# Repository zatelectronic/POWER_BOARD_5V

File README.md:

<div align="center">

# POWER BOARD +5V

**Placa de alimentação DC-DC step-down (buck converter) com entrada de 24V e saída regulada de 5V, baseada em regulador chaveado SMD de alta eficiência**

</div>

---

## 📋 Índice

- [POWER BOARD +5V](#power-board-5v)
  - [📋 Índice](#-índice)
  - [Visão Geral](#visão-geral)
  - [Renders 3D](#renders-3d)
  - [Funcionalidades](#funcionalidades)
  - [Diagrama de Funcionamento](#diagrama-de-funcionamento)
  - [Especificações Técnicas](#especificações-técnicas)
  - [Lista de Materiais](#lista-de-materiais)
  - [Pinagem dos Conectores](#pinagem-dos-conectores)
    - [DC IN — Entrada (lado esquerdo)](#dc-in--entrada-lado-esquerdo)
    - [DC OUT — Saída (lado direito)](#dc-out--saída-lado-direito)
    - [Pontos de Teste](#pontos-de-teste)
  - [Aplicações](#aplicações)
  - [Estrutura do Repositório](#estrutura-do-repositório)
  - [Como Usar](#como-usar)
    - [Instalação básica](#instalação-básica)
    - [Dica de Integração](#dica-de-integração)
  - [⚠️ Avisos de Segurança](#️-avisos-de-segurança)
  - [Sobre](#sobre)

---

## Visão Geral

**POWER BOARD +5V** é uma placa de alimentação DC-DC do tipo **buck converter (step-down)**, projetada pela **ZAT ELECTRONIC** utilizando **KiCad 10**. A placa converte uma tensão de entrada de **+24VDC** em uma saída regulada e estável de **+5VDC / 3A**, utilizando o regulador chaveado **LM2596S-5** no encapsulamento TO-263-5 (SMD).

O design é compacto e totalmente SMD, com conexões de entrada e saída por **pads de solda** expostos diretamente na PCB. A placa inclui **fusível de proteção SMD 3A**, **diodo Schottky** de roda livre, **indutor de 33µH** e capacitores eletrolíticos de alta capacidade para filtragem e estabilidade da saída.

> ⚡ Topologia **buck converter** de alta eficiência — ideal para sistemas embarcados, painéis de controle industrial e projetos que alimentam microcontroladores e periféricos a partir de fontes de 24VDC.

---

## Renders 3D

<div align="center">

*Vista superior — regulador LM2596S-5, indutor, capacitores eletrolíticos e fusível SMD*

<br/>

*Vista isométrica — layout compacto com pads DC IN e DC OUT nas extremidades*

</div>

---

## Funcionalidades

- ✅ **Regulador chaveado LM2596S-5** (TO-263-5 SMD) — saída fixa de 5V, até 3A
- ✅ **Topologia buck converter** — alta eficiência em comparação com reguladores lineares
- ✅ **Entrada 24VDC** — compatível com fontes industriais e painéis de automação
- ✅ **Saída 5VDC / 3A** — alimentação estável para microcontroladores e periféricos
- ✅ **Fusível SMD 3A** (encapsulamento 1808/2410) — proteção contra sobrecorrente na entrada
- ✅ **Diodo Schottky SS54** (SMA SMD) — diodo de roda livre de alta velocidade
- ✅ **Indutor 33µH** (12×12mm) — núcleo de potência para o estágio de conversão
- ✅ **Capacitor de entrada 100µF/35V** (SMD eletrolítico) — filtragem da tensão de entrada
- ✅ **Capacitor de saída 680µF/16V** (SMD eletrolítico) — filtragem e estabilidade da saída
- ✅ **4 pontos de teste (TP1–TP4)** — facilidade de medição e diagnóstico em bancada
- ✅ **Pads de conexão expostos** — DC IN (+24V / GND) e DC OUT (+5V / GND)
- ✅ **Layout totalmente SMD** — compacto e adequado para integração em painéis

---

## Diagrama de Funcionamento

```
DC IN (+24V) ──[F1 3A]──[D1 SS54]──┬──────────► VIN  [U1 LM2596S-5]  OUT ──┬──[L1 33µH]──┬──► DC OUT (+5V)
                                   │                       │                  │             │
                         [C1 100µF/35V]              GND / ~ON/OFF      [D2 SS54]     [C2 680µF/16V]
                                   │                       │            (roda livre)        │
                                  GND                     GND                 │            GND
                                                                             GND
                                    FB do U1 ◄──────────────────────────────────────── +5V

DC IN (GND) ──────────────────────────────────────────► DC OUT (GND)

TP1, TP2 → pontos de teste na entrada
TP3, TP4 → pontos de teste na saída
```

---

## Especificações Técnicas

| Parâmetro | Valor |
|-----------|-------|
| **Topologia** | Buck Converter (Step-Down) |
| **Regulador** | LM2596S-5 (TO-263-5 SMD) |
| **Tensão de Entrada** | 24VDC |
| **Tensão de Saída** | 5VDC (fixa) |
| **Corrente de Saída máx.** | 3A |
| **Potência máxima de saída** | 15W |
| **Diodo de roda livre** | SS54 — Schottky 5A / 40V (SMA SMD) |
| **Indutor** | 33µH — 12×12×8mm |
| **Capacitor de entrada** | 100µF / 35V (eletrolítico SMD) |
| **Capacitor de saída** | 680µF / 16V (eletrolítico SMD) |
| **Fusível** | 3A (SMD 1808/2410) |
| **Pontos de teste** | 4x (TP1, TP2, TP3, TP4) |
| **Conexões** | Pads de solda expostos (DC IN / DC OUT) |
| **Ferramenta de Projeto** | KiCad 10 |
| **Tipo de montagem** | SMD |

---

## Lista de Materiais

| Ref | Componente | Valor / Parte | Encapsulamento |
|-----|-----------|--------------|----------------|
| U1 | Regulador Chaveado | LM2596S-5 | TO-263-5 SMD |
| L1 | Indutor de Potência | 33µH | 12×12×8mm |
| D2 | Diodo Schottky (roda livre) | SS54 — 5A / 40V | SMA SMD |
| D1 | Diodo Schottky (proteção contra inversão) | SS54 — 5A / 40V | SMA SMD |
| C1 | Capacitor Eletrolítico (entrada) | 100µF / 35V | SMD Eletrolítico 10×10mm |
| C2 | Capacitor Eletrolítico (saída) | 680µF / 16V | SMD Eletrolítico 10×12,5mm |
| F1 | Fusível de Proteção | 3A | SMD 1808/2410 |
| TP1–TP4 | Pads de solda / teste | 10 × 4 mm | SMD |

---

## Pinagem dos Conectores

A placa utiliza **pads de solda expostos** nas extremidades para conexão da entrada e saída. Não há conectores PTH — a ligação é feita diretamente por fios soldados ou trilhas de PCB mãe.

### DC IN — Entrada (lado esquerdo)

| Pad | Sinal | Descrição |
|-----|-------|-----------|
| + | +24V | Tensão de entrada positiva |
| − | GND | Terra / Negativo |

### DC OUT — Saída (lado direito)

| Pad | Sinal | Descrição |
|-----|-------|-----------|
| + | +5V | Tensão de saída regulada |
| − | GND | Terra / Negativo |

### Pontos de Teste

| Ref | Localização | Função |
|-----|-------------|--------|
| TP1 | Entrada | Medição +24V |
| TP2 | Entrada | Medição GND entrada |
| TP3 | Saída | Medição +5V |
| TP4 | Saída | Medição GND saída |

---

## Aplicações

- 🏭 **Automação industrial** — alimentação de CLPs, sensores e módulos a partir de barramentos 24V
- 🤖 **Projetos com Arduino e ESP32** — conversão de 24V industrial para 5V de lógica
- 💡 **Painéis de iluminação LED** — alimentação de controladoras a partir de fonte 24V
- 🔌 **Sistemas embarcados** — fonte embarcada compacta em projetos de hardware customizado
- 📡 **IoT industrial** — alimentação de gateways e módulos de comunicação
- 🖥️ **Painéis de controle** — fonte auxiliar de 5V integrada ao painel principal 24V

---

## Estrutura do Repositório

```
POWER_BOARD_5V/
├── POWER_BOARD_5V.kicad_pro      # Arquivo de projeto KiCad 10
├── POWER_BOARD_5V.kicad_sch      # Esquemático: capa A2 (índice das folhas)
├── BUCK.kicad_sch                # Folha 02: buck LM2596S-5
├── CONN.kicad_sch                # Folha 03: pads DC IN / DC OUT + PWR_FLAG
├── POWER_BOARD_5V.kicad_pcb      # Layout da PCB (KiCad 10)
├── POWER_BOARD_5V.kicad_prl      # Configurações locais
├── POWER_BOARD_5V.kicad_dru      # Regras customizadas (vazio: version 1)
├── Zat_TitleBlock.kicad_wks      # Title block ZAT ELECTRONIC
├── packages3D/                   # Modelos 3D arquivados (referência)
├── imagem_1.png                  # Render 3D superior
├── imagem_2.png                  # Render 3D isométrico
├── LEIA-ME_REVISAO_R01.md        # O que mudou na revisão R01
└── README.md
```

---

## Como Usar

### Instalação básica

```
Fonte 24VDC (+) ────► Pad DC IN (+24V)
Fonte 24VDC (-) ────► Pad DC IN (GND)

Carga 5VDC      ────► Pad DC OUT (+5V)
Carga GND       ────► Pad DC OUT (GND)
```

### Dica de Integração

> 🔧 Para integração em PCB mãe, solde fios diretamente nos pads DC IN e DC OUT, ou projete a placa mãe com pads compatíveis para encaixe direto. Respeite a polaridade indicada na serigrafia (+24V / GND / +5V).

---

## ⚠️ Avisos de Segurança

> 🔴 **ATENÇÃO**

- **Não inverta a polaridade** na entrada — o fusível protege contra sobrecorrente, mas a inversão pode danificar o regulador.
- Respeite a **corrente máxima de 3A** na saída para não danificar o LM2596S-5.
- O regulador e o indutor podem **aquecer durante operação** em cargas próximas ao limite — garanta ventilação adequada.
- **Verifique a tensão de entrada** antes de conectar — tensões acima de 40V danificam o regulador.
- Utilize o **fusível SMD 3A** correto — nunca o substitua por um de valor superior sem analisar o circuito.

---

## Sobre

<div align="center">

Projetado por **ZAT ELECTRONIC**

*POWER BOARD +5V — Made in Brazil 🇧🇷*

</div>

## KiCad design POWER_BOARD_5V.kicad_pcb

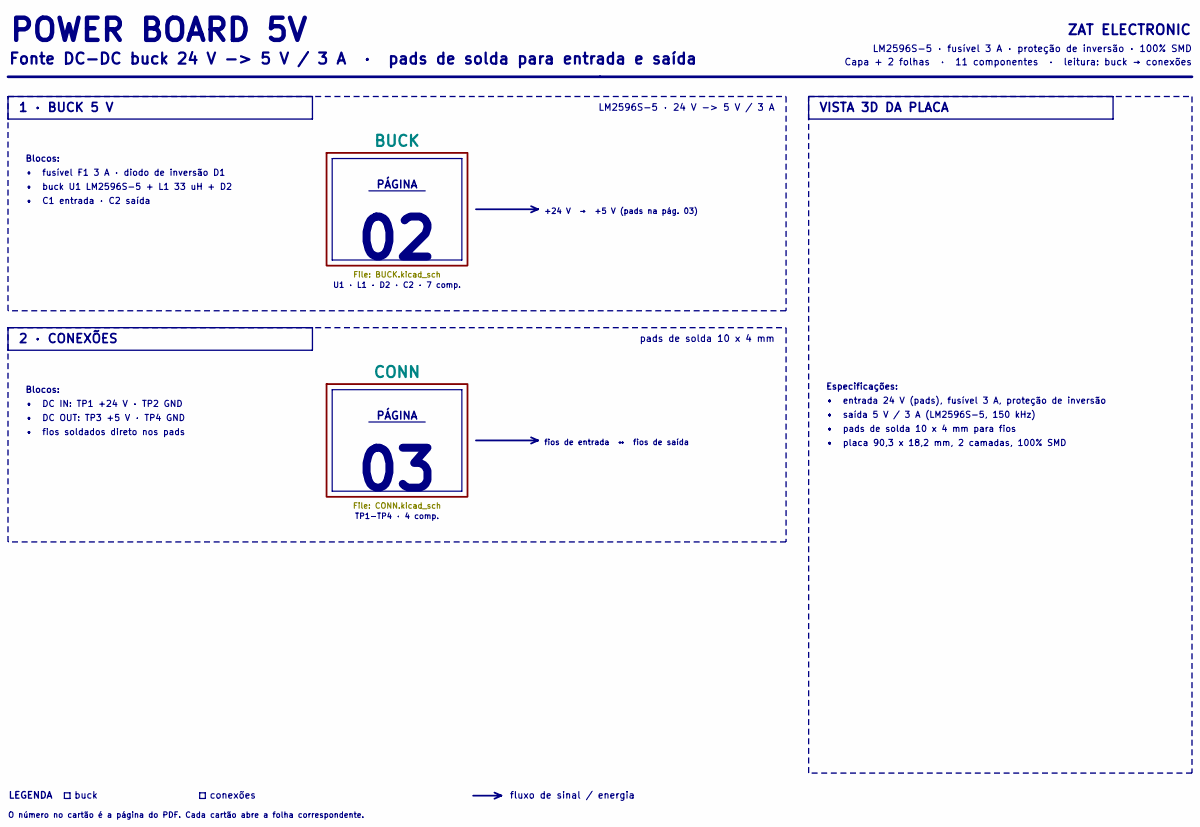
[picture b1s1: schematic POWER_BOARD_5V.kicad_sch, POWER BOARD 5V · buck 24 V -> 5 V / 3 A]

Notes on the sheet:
Capa + 2 folhas · 11 componentes · leitura: buck → conexões
Fonte DC-DC buck 24 V -> 5 V / 3 A · pads de solda para entrada e saída
buck
PÁGINA
• pads de solda 10 x 4 mm para fios
• DC OUT: TP3 +5 V · TP4 GND
• DC IN: TP1 +24 V · TP2 GND
conexões
• buck U1 LM2596S-5 + L1 33 uH + D2
VISTA 3D DA PLACA
• fios soldados direto nos pads
ZAT ELECTRONIC
1 · BUCK 5 V
Blocos:
• entrada 24 V (pads), fusível 3 A, proteção de inversão
LM2596S-5 · fusível 3 A · proteção de inversão · 100% SMD
fluxo de sinal / energia
LM2596S-5 · 24 V -> 5 V / 3 A
LEGENDA
pads de solda 10 x 4 mm
• C1 entrada · C2 saída
2 · CONEXÕES
+24 V → +5 V (pads na pág. 03)
Especificações:
• saída 5 V / 3 A (LM2596S-5, 150 kHz)
fios de entrada ↔ fios de saída
• placa 90,3 x 18,2 mm, 2 camadas, 100% SMD
• fusível F1 3 A · diodo de inversão D1
U1 · L1 · D2 · C2 · 7 comp.
POWER BOARD 5V
TP1-TP4 · 4 comp.
O número no cartão é a página do PDF. Cada cartão abre a folha correspondente.

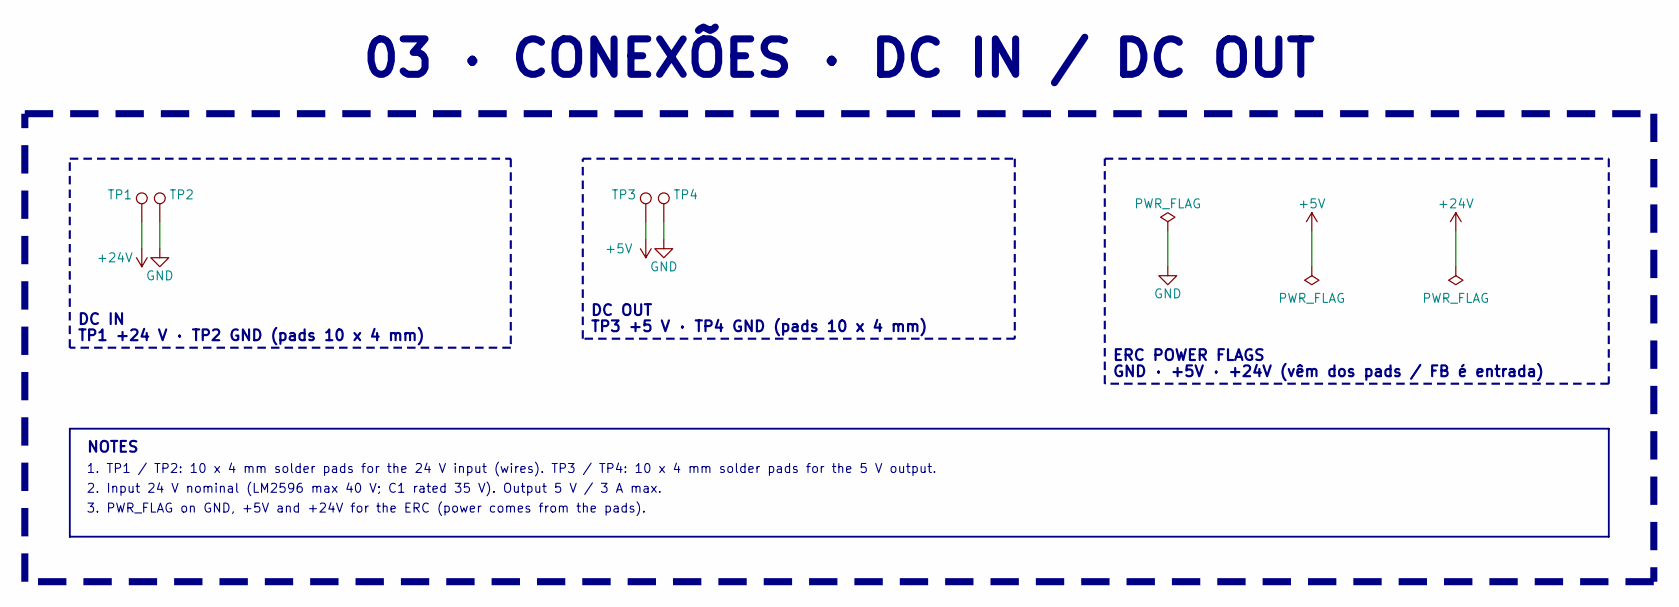
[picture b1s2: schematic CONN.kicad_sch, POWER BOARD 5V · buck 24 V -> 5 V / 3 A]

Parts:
TP1, TP2, TP3, TP4: PAD_10x4mm; TestPoint_Pad_10.0x4.0mm; MPN S1751-46R; Digi-Key_PN 952-1478-1-ND

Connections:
+5V: TP3.1 (1_1); also elsewhere on the board
+24V: TP1.1 (1_1); also elsewhere on the board
GND: TP2.1 (1_1), TP4.1 (1_1); also elsewhere on the board

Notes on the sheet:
ERC POWER FLAGS
2. Input 24 V nominal (LM2596 max 40 V; C1 rated 35 V). Output 5 V / 3 A max.
GND · +5V · +24V (vêm dos pads / FB é entrada)
NOTES
03 · CONEXÕES · DC IN / DC OUT
DC IN
DC OUT
TP3 +5 V · TP4 GND (pads 10 x 4 mm)
TP1 +24 V · TP2 GND (pads 10 x 4 mm)
1. TP1 / TP2: 10 x 4 mm solder pads for the 24 V input (wires). TP3 / TP4: 10 x 4 mm solder pads for the 5 V output.
3. PWR_FLAG on GND, +5V and +24V for the ERC (power comes from the pads).

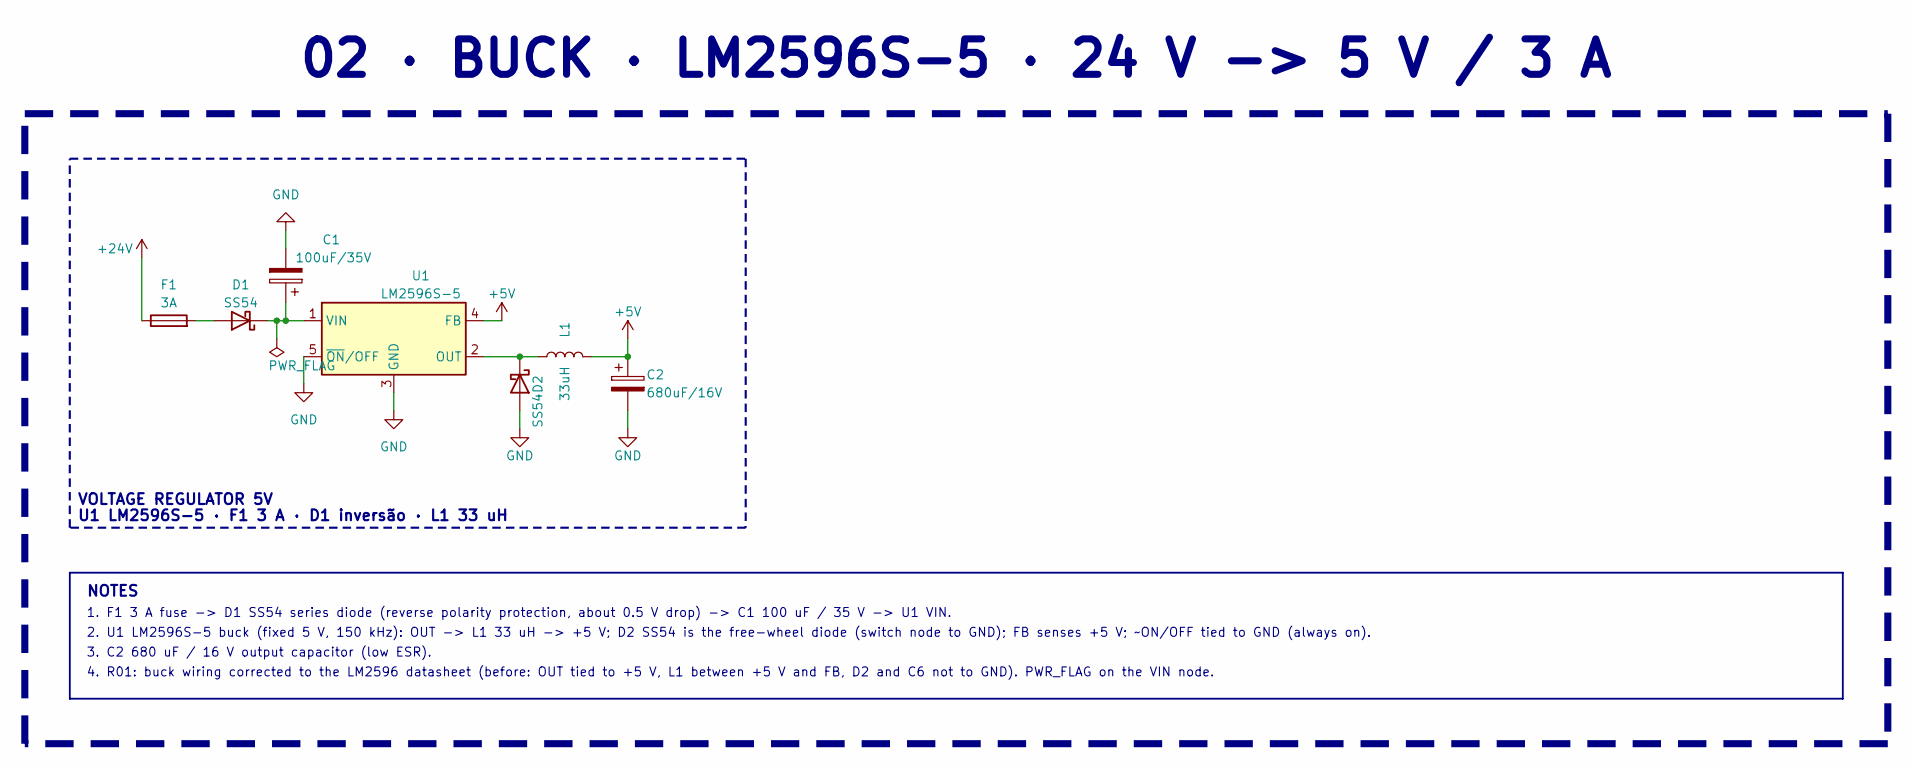
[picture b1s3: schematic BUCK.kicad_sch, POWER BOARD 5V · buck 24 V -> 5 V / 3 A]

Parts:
C1: 100uF/35V; CP_Elec_10x10
C2: 680uF/16V; CP_Elec_10x12.5
D1, D2: SS54; D_SMA
F1: 3A; Fuse_2010_5025Metric_Pad1.52x2.65mm_HandSolder_1808-2410
L1: 33uH; L_12x12mm_H8mm_33uH
U1: LM2596S-5; TO-263-5_TabPin3

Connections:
+5V: C2.1, L1.1, U1.4 (FB); also elsewhere on the board
+24V: F1.1; also elsewhere on the board
GND: C1.2, C2.2, D2.2 (A), U1.3 (GND), U1.5 (~ON/OFF); also elsewhere on the board
unnamed: D1.2 (A), F1.2
unnamed: C1.1, D1.1 (K), U1.1 (VIN)
unnamed: D2.1 (K), L1.2, U1.2 (OUT)

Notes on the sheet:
U1 LM2596S-5 · F1 3 A · D1 inversão · L1 33 uH
2. U1 LM2596S-5 buck (fixed 5 V, 150 kHz): OUT -> L1 33 uH -> +5 V; D2 SS54 is the free-wheel diode (switch node to GND); FB senses +5 V; ~ON/OFF tied to GND (always on).
02 · BUCK · LM2596S-5 · 24 V -> 5 V / 3 A
NOTES
VOLTAGE REGULATOR 5V
4. R01: buck wiring corrected to the LM2596 datasheet (before: OUT tied to +5 V, L1 between +5 V and FB, D2 and C6 not to GND). PWR_FLAG on the VIN node.
3. C2 680 uF / 16 V output capacitor (low ESR).
1. F1 3 A fuse -> D1 SS54 series diode (reverse polarity protection, about 0.5 V drop) -> C1 100 uF / 35 V -> U1 VIN.

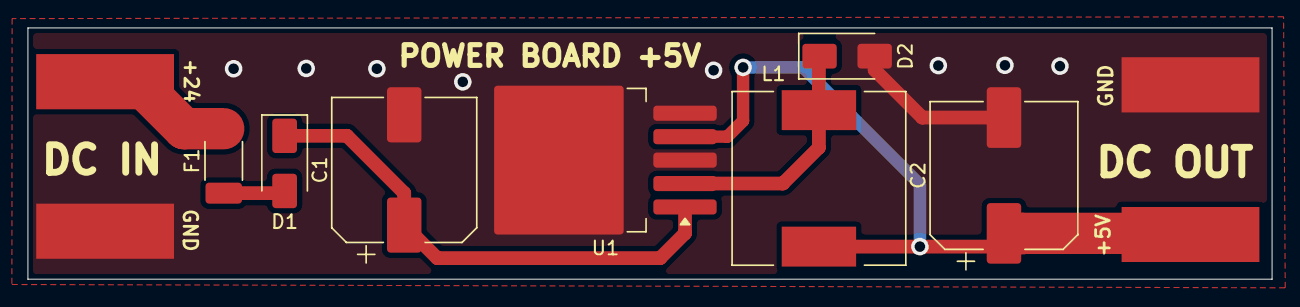
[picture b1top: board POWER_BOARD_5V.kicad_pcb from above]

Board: 2 copper layers, 90.3 x 18.2 mm, 11 parts (0 on the bottom side), 6 nets.

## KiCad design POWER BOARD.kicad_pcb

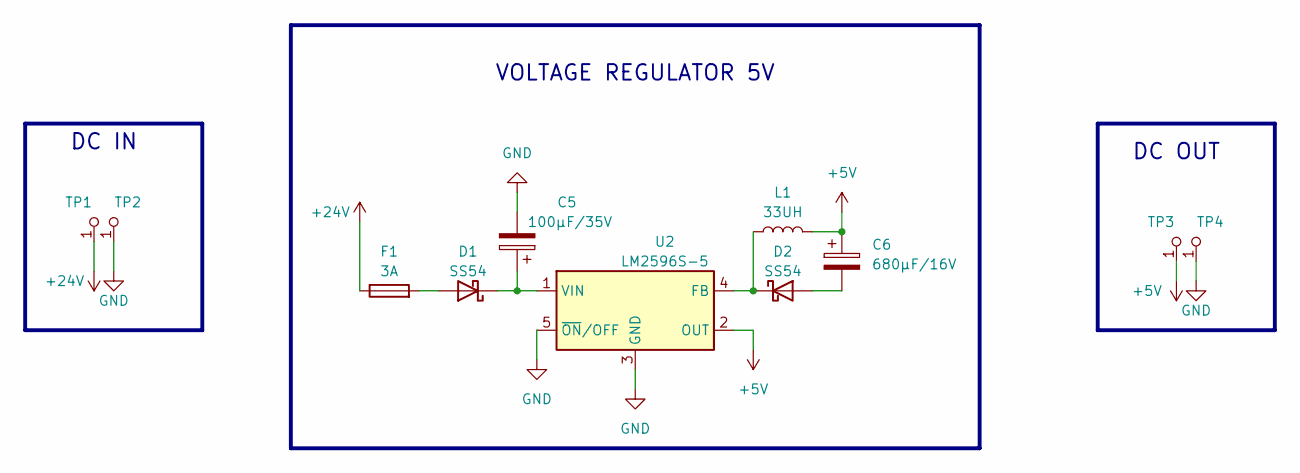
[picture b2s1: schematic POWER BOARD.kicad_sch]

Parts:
C5: 100μF/35V; CP_Elec_10x10
C6: 680μF/16V; CP_Elec_10x12.5
D1, D2: SS54; D_SMA
F1: 3A; Fuse_2010_5025Metric_Pad1.52x2.65mm_HandSolder
L1: 33UH; L_12x12mm_H8mm
TP1, TP2, TP3, TP4: S1751-46R; Test_Point_2.67x1.02mm; MPN S1751-46R; Digi-Key_PN 952-1478-1-ND
U2: LM2596S-5; TO-263-5_TabPin3

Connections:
+5V: C6.1, L1.1, TP3.1, U2.2 (OUT)
+24V: F1.1, TP1.1
GND: C5.2, TP2.1, TP4.1, U2.3 (GND), U2.5 (~ON/OFF)
unnamed: D1.2 (A), F1.2
unnamed: C5.1, D1.1 (K), U2.1 (VIN)
unnamed: C6.2, D2.2 (A)
unnamed: D2.1 (K), L1.2, U2.4 (FB)

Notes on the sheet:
DC OUT
DC IN
VOLTAGE REGULATOR 5V

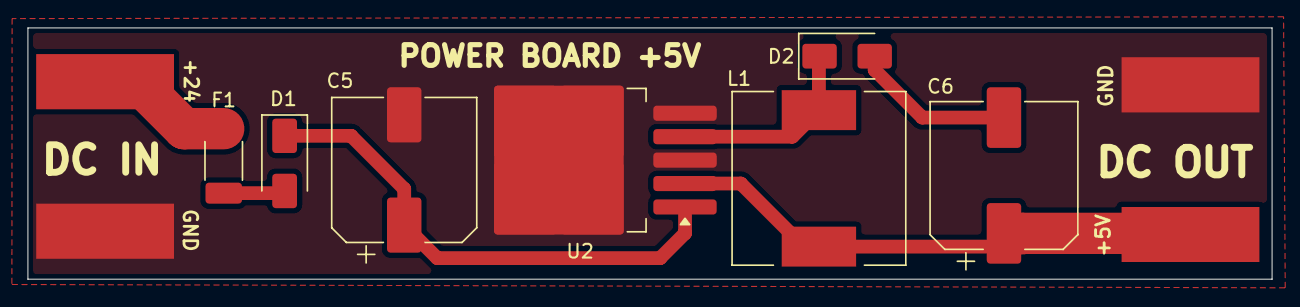
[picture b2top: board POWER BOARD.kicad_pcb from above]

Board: 2 copper layers, 90.3 x 18.2 mm, 11 parts (0 on the bottom side), 7 nets.

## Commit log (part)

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2026-06-28 commit_3
2026-06-29 COMMIT-4
